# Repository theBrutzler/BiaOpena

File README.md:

# BiaOpena
 a not beerbottleopener

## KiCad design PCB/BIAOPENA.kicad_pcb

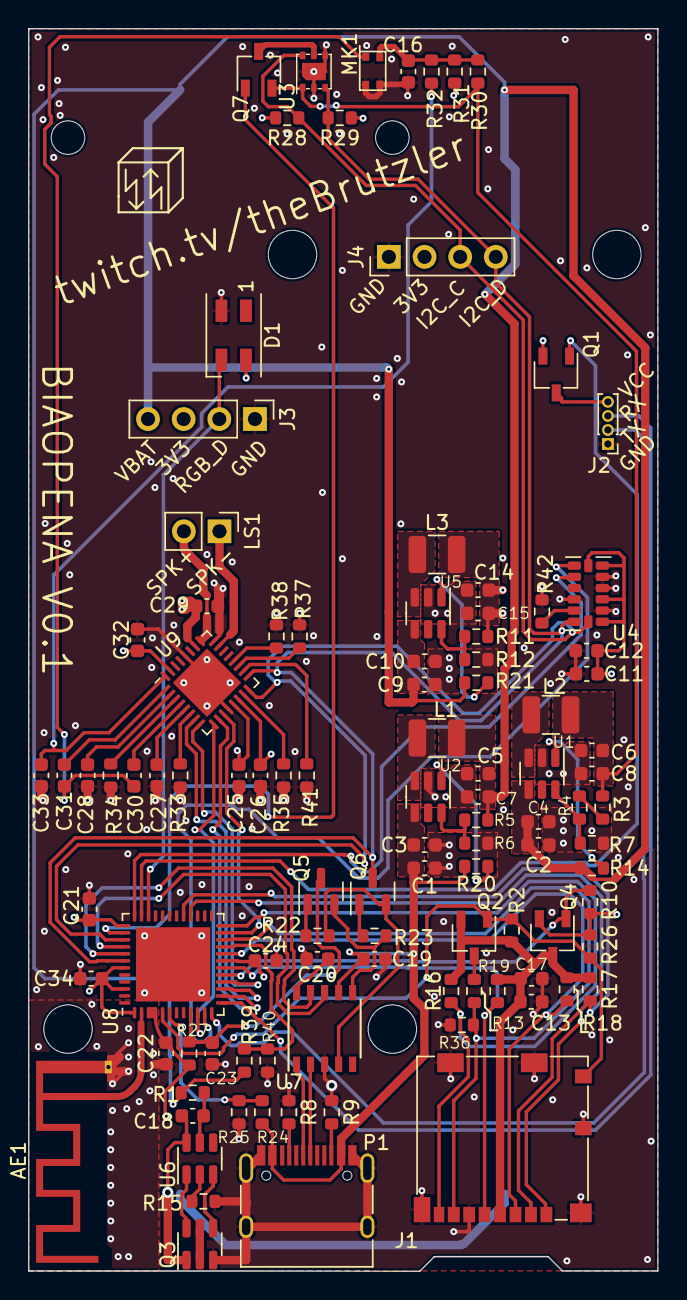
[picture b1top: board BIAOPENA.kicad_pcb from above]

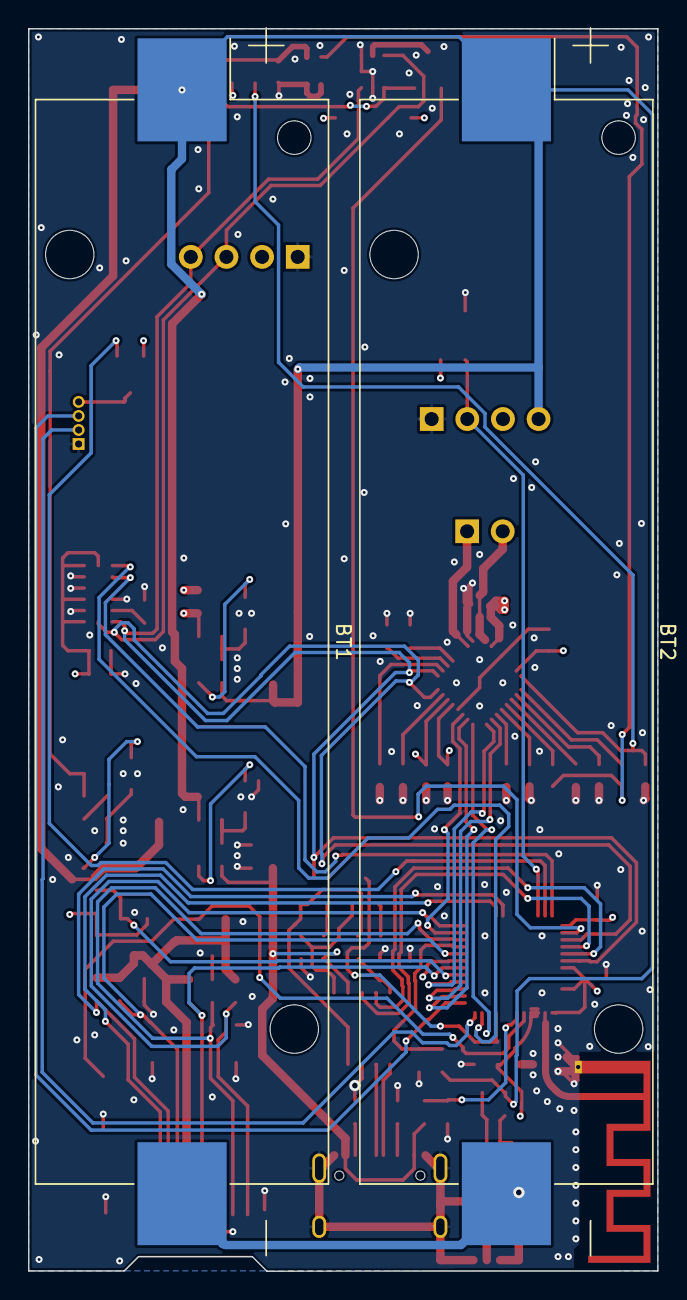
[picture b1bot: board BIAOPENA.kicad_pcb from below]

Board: 4 copper layers, 44.8 x 88.5 mm, 107 parts (2 on the bottom side), 78 nets.

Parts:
AE1: Antenna_Dipole; Texas_SWRA117D_2.4GHz_Left
BT1, BT2: 18650; BatteryHolder_Keystone_1042_1x18650
C1, C2, C7, C8, C9, C15, C17, C21, C25, C26, C27, C28, C29, C30, C31, C32, C33, C34: 4µ7; C_0603_1608Metric
C3, C4, C5, C6, C10, C12, C14, C16, C18, C22, C23, C24: 100n; C_0603_1608Metric
C11: 1µ; C_0603_1608Metric
C13, C19, C20: 220n; C_0603_1608Metric
D1: SK6812MINI; LED_SK6812MINI_PLCC4_3.5x3.5mm_P1.75mm
J1: Micro_SD_Card_Det; microSD_HC_Molex_104031-0811
J2: Conn_01x04_Female; PinHeader_1x04_P1.00mm_Vertical
J3, J4: Conn_01x04_Female; PinHeader_1x04_P2.54mm_Vertical
L1, L2, L3: 2u2; L_1210_3225Metric
LS1: Speaker; PinHeader_1x02_P2.54mm_Vertical
MK1: AP2718AT
P1: USB_C_Plug_USB2.0; USB_C_Receptacle_HRO_TYPE-C-31-M-12
Q1, Q2, Q4, Q7: DMG2301L-7; TSOT-23
Q3: FS8205A; SOT-23-6
Q5, Q6: Q_NPN_BEC; SOT-23
R1: 100; R_0603_1608Metric
R2, R3, R4, R6, R7, R10, R12, R24, R25, R26, R36, R39, R40: 100K; R_0603_1608Metric
R5: 590K; R_0603_1608Metric
R8, R9, R13, R16, R17, R18, R19, R22, R23: 5K1; R_0603_1608Metric
R11: 430K; R_0603_1608Metric
R14, R15, R20, R21, R27, R28, R29: 1K; R_0603_1608Metric
R30, R31, R32, R33, R34, R35, R37, R38, R41, R42: 0; R_0603_1608Metric
SM3: SYM_Arrow45_Tiny; Symbol_kurzschlussblog
U1, U2, U5: MT3420C-mt3420c; SOT-23-6
U3: SGP30; SGP30-DFN6_2,45x2,45_TP
U4: ADXL343; LGA-14_3x5mm_P0.8mm_LayoutBorder1x6y
U6: DW01A; SOT-23-6
U7: CH340K; SSOP-10_3.9x4.9mm_P1.00mm
U8: ESP32-PICO-D4; QFN-48-1EP_7x7mm_P0.5mm_EP5.3x5.3mm
U9: WM8978; QFN-32-1EP_5x5mm_P0.5mm_EP3.45x3.45mm

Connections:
+1V8: C6.2, C8.2, L2.2, Q7.2 (S), R3.2, R30.1, U3.1 (VDD)
+3V3: C11.1, C12.1, C14.2, C15.2, C21.2, C22.2, C24.2, C25.1, C26.1, C29.1, C32.1, C34.2, D1.4 (VDD), J3.3, J4.2, L3.2, Q1.2 (S), Q4.2 (S), R10.1, R11.1, R26.2, R27.1, R28.2, R29.1, R31.2, U4.1 (Vdd_I/O), U4.3 (RES), U4.6 (Vs), U4.7 (~CS), U8.1 (VDDA), U8.3 (VDDA3P3), U8.4 (VDDA3P3), U8.19 (VDD3P3_RTC), U8.37 (VDD3P3_CPU), U8.43 (VDDA), U8.46 (VDDA), U9.13 (DCVDD), U9.14 (DBVDD), U9.26 (SPKVDD), U9.31 (AVDD)
+5V: C1.2, C3.2, C19.1, P1.A4 (VBUS), P1.A9 (VBUS), P1.B4 (VBUS), P1.B9 (VBUS), R20.1, R24.1, U2.4 (IN), U7.7 (VCC)
+BATT: BT1.1 (+), BT2.1 (+), C2.2, C4.2, C5.2, C7.2, C9.2, C10.2, J3.4, L1.2, R1.2, R5.1, R14.1, R21.1, R39.1, U1.4 (IN), U5.4 (IN)
ACC_INT1: U4.8 (INT1), U8.11 (IO35)
ACC_INT2: U4.9 (INT2), U8.36 (IO23)
BIAS: C33.1, R32.2, U9.32 (MICBIAS)
COD_RX: J2.3, U8.13 (IO33)
COD_TX: J2.2, U8.12 (IO32)
COD_nEN: Q1.1 (G), U8.35 (IO18)
ESP_~RST: C23.1, Q5.3 (C), R27.2, U8.9 (EN)
GAS_nEN: Q7.1 (G), U8.38 (IO19)
GND: AE1.2, C1.1, C2.1, C3.1, C4.1, C5.1, C6.1, C7.1, C8.1, C9.1, C10.1, C11.2, C12.2, C13.2, C14.1, C15.1, C16.2, C17.1, C19.2, C20.2, C21.1, C22.1, C23.2, C24.1, C25.2, C26.2, C27.2, C28.2, C29.2, C32.2, C33.2, C34.1, D1.2 (VSS), J1.6 (VSS), J1.9 (DET_B), J1.11 (SHIELD), J2.1, J3.1, J4.1, MK1.2 (GND), MK1.3 (GND), P1.A1 (GND), P1.A12 (GND), P1.B1 (GND), P1.B12 (GND), P1.S1 (SHIELD), Q3.3 (S), R6.2, R7.2, R8.1, R9.1, R12.2, R15.1, R25.2, R33.2, R34.2, R35.2, R36.1, R37.2, R38.2, R40.2, R41.1, R42.2, U1.2 (GND), U2.2 (GND), U3.2 (GND), U3.4 (R), U3.7 (GND), U4.2 (GND), U4.4 (GND), U4.5 (GND), U4.11 (RES), U5.2 (GND), U7.3 (GND), U8.49 (GND), U9.12 (DGND), U9.24 (SPKGND), U9.28 (AGND), U9.33 (GND_PAD)
I2C_CLK: J4.3, R28.1, U3.6 (SCL), U4.14 (SCL/SCLK), U8.39 (IO22), U9.16 (SCLK)
I2C_DAT: J4.4, Q6.3 (C), R29.2, U3.3 (SDA), U4.13 (SDA/SDI/SDIO), U8.42 (IO21), U9.17 (SDIN)
I2S_BCLK: U8.16 (IO27), U9.8 (BCLK)
I2S_DIN: U8.10 (IO34), U9.9 (ADCDAT)
I2S_DOUT: U8.14 (IO25), U9.10 (DACDAT)
I2S_LRC_WS: U8.15 (IO26), U9.7 (LRC)
I2S_MCLK: U8.23 (IO0), U9.11 (MCLK)
unnamed: AE1.1, U8.2 (LNA_IN)
unnamed: BT1.2 (-), BT2.2 (-), C18.1, Q3.1 (S), U6.6 (GND)
unnamed: C13.1, C17.2, J1.4 (VDD), Q2.2 (S), Q4.3 (D), R2.2, R16.1, R17.1, R18.1, R19.1
unnamed: C16.1, MK1.4 (VCC), R30.2, R31.1, R32.1
unnamed: C18.2, R1.1, U6.5 (VCC)
unnamed: C20.1, U7.10 (V3)
unnamed: C27.1, U9.5 (RIN)
unnamed: C28.1, U9.2 (LIN)
unnamed: C30.1, U9.4 (RIP)
unnamed: C30.2, C31.2, MK1.1 (OUT)
unnamed: C31.1, U9.1 (LIP)
unnamed: D1.3 (DIN), J3.2, U8.34 (IO5)
unnamed: J2.4, Q1.3 (D)
unnamed: L1.1, U2.3 (SW)
unnamed: L2.1, U1.3 (SW)
unnamed: L3.1, U5.3 (SW)
unnamed: LS1.1, U9.23 (ROUT2)
unnamed: LS1.2, U9.25 (LOUT2)
unnamed: P1.A5 (CC), R8.2
unnamed: P1.A6 (D+), U7.1 (UD+)
unnamed: P1.A7 (D-), U7.2 (UD-)
unnamed: P1.B5 (VCONN), R9.2
unnamed: Q2.3 (D), R13.2
unnamed: Q3.2 (D), Q3.5 (D)
unnamed: Q3.4 (G), U6.3 (OC)
unnamed: Q3.6 (G), U6.1 (OD)
unnamed: Q5.1 (B), R22.1
unnamed: Q5.2 (E), R23.2, U7.6 (~RTS)
unnamed: Q6.1 (B), R23.1
unnamed: Q6.2 (E), R22.2, U7.4 (~DTR)
unnamed: Q7.3 (D), U3.5 (VDDH)
unnamed: R3.1, R4.1
unnamed: R4.2, R7.1, U1.6 (FB)
unnamed: R5.2, R6.1, U2.6 (FB)
unnamed: R11.2, R12.1, U5.6 (FB)
unnamed: R14.2, U1.1 (EN)
unnamed: R15.2, U6.2 (VM)
unnamed: R20.2, U2.1 (EN)
unnamed: R21.2, U5.1 (EN)
unnamed: R24.2, R25.1, U8.6 (SENSOR_CAPP)
unnamed: R33.1, U9.6 (R2/GPIO3)
unnamed: R34.1, U9.3 (L2/GPIO2)
unnamed: R35.1, U9.15 (CSB/GPIO1)
unnamed: R37.1, U9.19 (AUXL)
unnamed: R38.1, U9.20 (AUXR)
unnamed: R39.2, R40.1, U8.21 (IO15)
unnamed: R41.2, U9.18 (MODE)
unnamed: R42.1, U4.12 (SDO/ADDR)
SD_CLK: J1.5 (CLK), R19.2, U8.18 (IO12)
SD_DAT0: J1.7 (DAT0), R13.1, R36.2, U8.22 (IO2)
SD_DAT1: J1.8 (DAT1), R16.2, U8.24 (IO4)
SD_DAT2: J1.1 (DAT2), U8.28 (SD2/IO9)
SD_DAT3: J1.2 (DAT3/CD), R17.2, U8.29 (SD3/IO10)
SD_VCC_nEN: Q4.1 (G), R10.2, U8.17 (IO14)
SD_nCS: J1.3 (CMD), R18.2, U8.20 (IO13)
SD_nDET: J1.10 (DET_A), Q2.1 (G), R2.1, R26.1, U8.5 (SENSOR_VP)
UART1_RX: U7.9 (RXD), U8.41 (U0TXD/IO1)
UART1_TX: U7.8 (TXD), U8.40 (U0RXD/IO3)

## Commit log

2022-11-02 Initial Upload
    Untested initial upload
    Software not working as expected
